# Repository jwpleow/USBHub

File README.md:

## Impedance Control
Impedance control was done assuming manufacturing using JLCPCB 6 layer PCB JLC06161H-7628
90Ohms Diff Pair (usb) -> 0.127mm spacing, 0.16mm trace width
100Ohms Diff Pair (ethernet) -> 0.127mm spacing, 0.11mm trace width

## Min vias
We require 0.15mm/0.25mm vias ($$$$$$$$$$$$)

### Red LED for PD fault
KT-0603R
https://jlcpcb.com/partdetail/Hubei_KentoElec-KT0603R/C2286

## Power
### 5V
| Part Name | Description | Datasheet | JLCPCB |
| - | - | - | - |
| TPS56637RPAR | 4.5-V to 24-V In, 0.6-V to 7-V Out, 8-A Synchronous Step-Down Voltage Regulator | [Datasheet](https://www.ti.com/lit/ds/symlink/tps51396a.pdf) | [JLCPCB](https://jlcpcb.com/partdetail/TexasInstruments-TPS56637RPAR/C841386) | 
| FXL0630-3R3-M | Inductor 3.3uH (max 22mOhm) 8.5A | | [JLCPCB](https://jlcpcb.com/partdetail/178602-FXL0630_3R3M/C167219) |

### 3V3
| Part Name | Description | Datasheet | JLCPCB |
| - | - | - | - |
| TLV75733PDBVR |  Fixed 3.3V 1A SOT-23-5 25uA qI | | [JLCPCB](https://jlcpcb.com/partdetail/TexasInstruments-TLV75733PDBVR/C485517) |

### 1V2
| Part Name | Description | Datasheet | JLCPCB |
| - | - | - | - |
| TPS54331DR | Step-down type Adjustable 0.8V~25V 3A 3.5V~28V Buck converter | [Datasheet](https://www.ti.com/lit/ds/symlink/tps54331.pdf) | [JLCPCB](https://jlcpcb.com/partdetail/TexasInstruments-TPS54331DR/C9865) |
| FNR6045S180MT | Inductor 18uH ±20% 2.4A SMD,6x6mm, 81mOhm |  | [JLCPCB](https://jlcpcb.com/partdetail/179462-FNR6045S180MT/C168079) |

## USB
### Power Delivery

| Part Name | Description | Datasheet | JLCPCB |
| - | - | - | - |
| CYPD3177_24LQXQ | USB Type-C and Power Delivery (PD) Controller QFN-24 | [Datasheet](https://www.infineon.com/dgdl/Infineon-EZ-PD_BCR_Datasheet_USB_Type-C_Port_Controller_for_Power_Sinks-DataSheet-v03_00-EN.pdf?fileId=8ac78c8c7d0d8da4017d0ee7ce9d70ad) | [JLCPCB](https://jlcpcb.com/partdetail/CypressSemicon-CYPD317724LQXQ/C2959321) | 
| BZT52C12 | Zener Diode | | [JLCPCB](https://jlcpcb.com/partdetail/Goodwork-BZT52C12/C2932744) | 
| SI3421DV-T1-GE3 | PMOSFET | | [JLCPCB](https://jlcpcb.com/partdetail/VishayIntertech-SI3421DV_T1GE3/C144884) | 
| SS54 | Schottky Diode for Reverse Polarity Protection | | [JLCPCB](https://jlcpcb.com/partdetail/Hongjiacheng-SS54/C7420369) |

### USB Data

| Part Name | Description | Datasheet | JLCPCB |
| - | - | - | - |
| CYUSB3304-68LTXCT | USB 3.2 Gen1 4-port Hub Controller | [Datasheet](https://www.infineon.com/dgdl/Infineon-CYUSB330x_CYUSB331x_CYUSB332x_HX3_USB_3.0_Hub-DataSheet-v21_00-EN.pdf?fileId=8ac78c8c7d0d8da4017d0ecb53f644b8) | [JLCPCB](https://jlcpcb.com/partdetail/CypressSemicon-CYUSB330468LTXCT/C914921) |
| TUSB522PPRGER | 5Gbps USB3.0 redriver | [Datasheet](https://www.ti.com/lit/ds/symlink/tusb522p.pdf) | [JLCPCB](https://jlcpcb.com/parts/componentSearch?searchTxt=TUSB522P)  |
| PI3USB302-AZBEX | USB 3.0 Passive mux | [Datasheet](https://www.diodes.com/assets/Datasheets/PI3USB302-A.pdf) |  [JLCPCB](https://jlcpcb.com/partdetail/DiodesIncorporated-PI3USB302AZBEX/C500787) |
| TXM26M0004322CBCDO00T | Crystal for USB Hub Controller 26MHz +- 10ppm 9pF | | [JLCPCB](https://jlcpcb.com/partdetail/Yajingxin-TXM26M0004322CBCDO00T/C362346) |
<!-- | TUSB212IRWBR | USB 2.0 Signal Conditioner | [Datasheet](https://www.ti.com/lit/ds/symlink/tusb212.pdf) | [JLCPCB](https://jlcpcb.com/partdetail/TexasInstruments-TUSB212IRWBR/C2674396) | -->

### USB Ancillaries
| Part Name | Description | Datasheet | JLCPCB |
| - | - | - | - |
| GT-USB-7052 | USB Type-C Receptacle USB3.1 5A 24 Pins Vertical SMD | [Datasheet](https://www.dg-switch.com/uploads/soft/200510/GT-USB-7052.pdf) | [JLCPCB](https://jlcpcb.com/partdetail/gswitch-GT_USB7052/C963223) |
| PUSB3FR4Z | ESD Protection for differential pairs | [Datasheet](https://assets.nexperia.com/documents/data-sheet/PUSB3FR4.pdf) | [JLCPCB](https://jlcpcb.com/partdetail/Nexperia-PUSB3FR4Z/C503418)  |
| TI TVS2200DRVR | ESD Protection 28V for VBUS | [Datasheet](https://www.ti.com/lit/ds/symlink/tvs2200.pdf) | [JLCPCB](https://jlcpcb.com/partdetail/TexasInstruments-TVS2200DRVR/C523793) |
| TPS2069CDBVR | 1.5A Current limiting power distribution switch for USB DFP | [Datasheet](https://www.ti.com/lit/ds/symlink/tps2001c.pdf) | [JLCPCB](https://jlcpcb.com/partdetail/TexasInstruments-TPS2069CDBVR/C181752) |
| ESD5B5.0ST1G | 5.8V ESD Protection for DFP VBUS | [Datasheet](https://www.onsemi.com/pdf/datasheet/esd5b5.0st1-d.pdf) | [JLCPCB](https://jlcpcb.com/partdetail/Onsemi-ESD5B50ST1G/C93623) | 
| 484080003 | USB Type A Vertical | | [JLCPCB](https://jlcpcb.com/partdetail/Molex-484080003/C587839) |

### Ethernet USB 
| Part Name | Description | Datasheet | JLCPCB |
| - | - | - | - |
| RTL8153B-VB-CG | Ethernet-USB controller |  | [JLCPCB](https://jlcpcb.com/partdetail/RealtekSemicon-RTL8153B_VBCG/C2802072)  |
| G24P02S | RJ45 Transformer | | [JLCPCB](https://jlcpcb.com/partdetail/Jasn-G24P02S/C2827276)  |
| 7D025000Q01 | 25MHz Crystal, 18pF +- 10ppm | | [JLCPCB](https://jlcpcb.com/partdetail/Hd-7D025000Q01/C648942)|
| RC01931 | Ethernet Port Vertical | | [JLCPCB](https://jlcpcb.com/partdetail/Rch-RC01931/C708651) |

### Others
| Part Name | Description | Datasheet | JLCPCB |
| - | - | - | - |
| KT-0805G | LED Green | | [JLCPCB](https://jlcpcb.com/partdetail/Hubei_KentoElec-KT0805G/C2297) |
| BLM21PG221SN1D | Ferrite Bead 2A @ 85C | | [JLCPCB](https://jlcpcb.com/partdetail/MurataElectronics-BLM21PG221SN1D/C85840) |
| WJ103-5.0-2P | 2P 5mm screw terminal angled | | [JLCPCB](https://jlcpcb.com/partdetail/Ningbo_KangnexElec-WJ103_5_02P/C8439 )  |
| RVT1V151M0607 | 150u Aluminium Electrolytic Capacitor | | [JLCPCB](https://jlcpcb.com/partdetail/Roqang-RVT1V151M0607/C3032176) |
 <!-- | TI TPDxE05U06 | ESD Protection TVS 28V for CC / DP / DM?  | [Datasheet](https://www.ti.com/lit/ds/symlink/tpd4e05u06.pdf) | [JLCPCB](https://jlcpcb.com/partdetail/TexasInstruments-TPD4E05U06DQAR/C138714)  -->

## Buck Converter to 5V

## USB Hub Design Checklist
1 Are the decoupling capacitors and bulk capacitors connected as per Figure 1 and Figure 2? Y
2 Does the crystal meet the specification in this application note?  Y
3 Are all DS ports provided with 150-µF bulk capacitors? Y
4 Do the Power-on-Reset RC components meet the minimum reset time (5 ms)? Y
5 Do the USB precision resistors have 1% tolerance?  Y
6 Are the I2C lines provided with pull-up resistors to the 3.3-V domain? Y
7 Do the LEDs connected to the pin-strap pins have a 10-kΩ parallel resistor? Y
8
Is it ensured that the DS port power switch has a MOSFET connected to the OUTPUT pin or selected a power switch with
fast discharge? Y
9 Is the VBUS_US pin provided with a 10-kΩ voltage divider network? Y
10 Is the US port provided with 1-µF bulk capacitor? N
11 Are all port shields terminated properly?
12 Are the ferrite beads connected as shown in Figure 1 and Figure 2?
13
Are MODE_SEL[1] and MODE_SEL[0] not pulled LOW when the pin-strap configuration is used with HX3? (For 88-pin
QFN only).
14
Are values of the resistors connected in series to the LEDs decided based on the HX3’s I/O current source/sink capability
(4 mA)?
Layout Checklist
1 Is the crystal placed close to the chip (less than 1 cm)?
2 Are the decoupling capacitors and bulk capacitors placed close to the HX3 power pins?
3 Are the vias placed close to the HX3 power pins?
4 Are the power traces routed away from the high-speed data lines and the clock lines?
5 Is the capacitor in the RC reset circuitry placed close to the reset pin of HX3?
6 Is the 150-µF capacitor placed close to the DS port connector?
7 Are the USB SS and HS signal lines matched in length?
8 Are the USB data lines provided with solid ground plane underneath?
9 Are the SS traces provided with the guard traces along the USB data trace with stitching vias?
10 Are the SS traces provided with the AC decoupling capacitors (0.1 µF) on the TX lines?
11 Are the USB traces kept as short as possible?
12 Is it ensured that there are no stubs on all the USB traces?
13 Is it ensured that there are no vias on the SS traces?
14 Do the USB traces have few bends and no 90-degree bends?

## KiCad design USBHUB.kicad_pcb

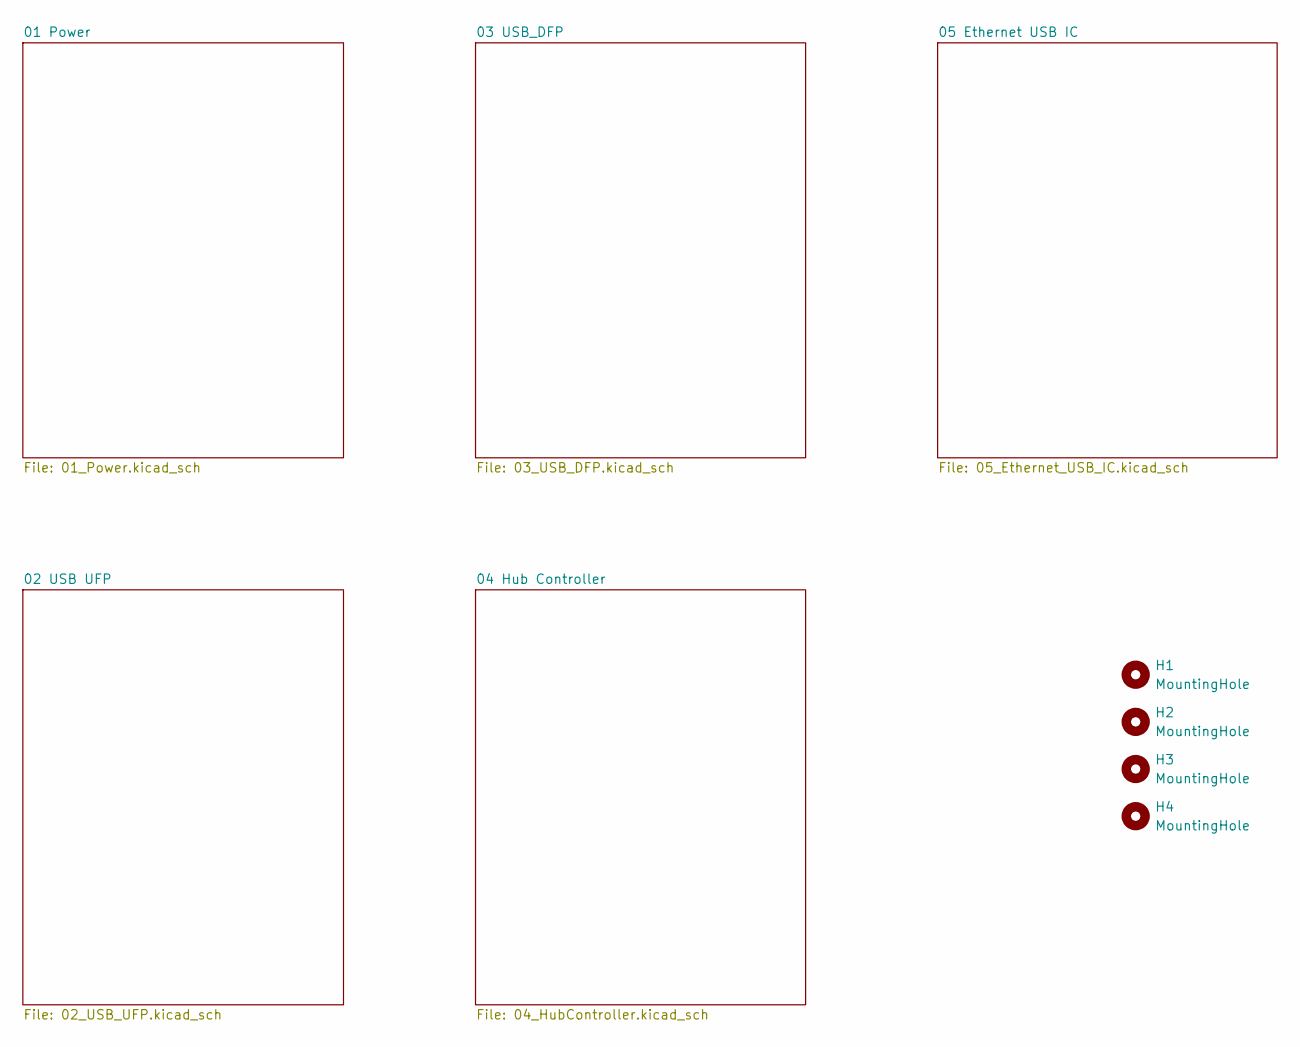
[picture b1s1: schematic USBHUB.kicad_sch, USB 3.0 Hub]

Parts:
H1, H2, H3, H4: MountingHole; MountingHole_2.7mm_M2.5

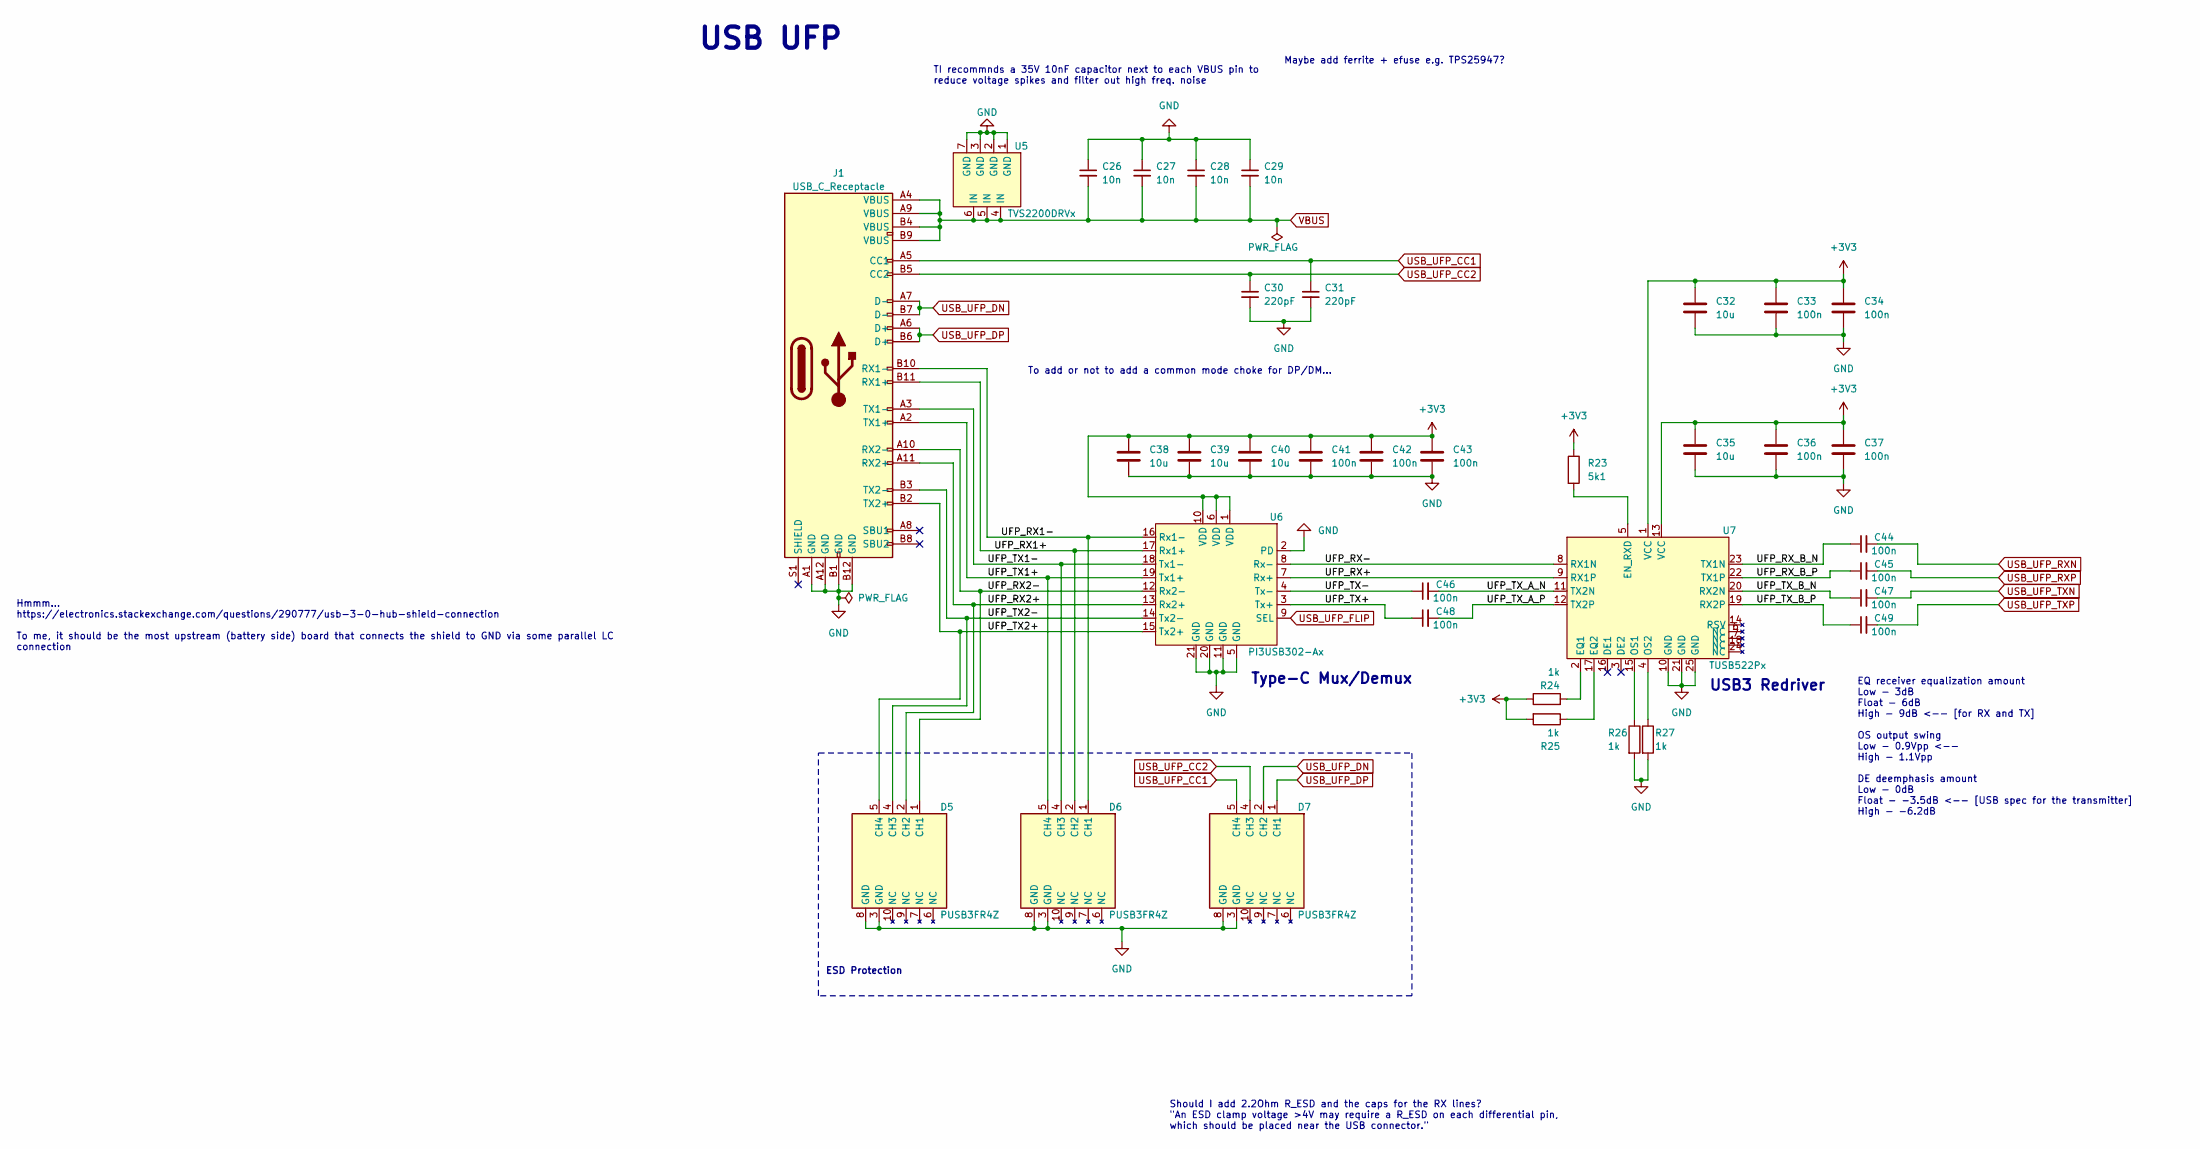
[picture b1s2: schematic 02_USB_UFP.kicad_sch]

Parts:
C26, C27, C28, C29: 10n; C_0402_1005Metric
C30, C31: 220pF; C_0402_1005Metric
C32, C35, C38, C39, C40: 10u; C_0603_1608Metric
C33, C34, C36, C37, C41, C42, C43, C44, C45, C46, C47, C48, C49: 100n; C_0402_1005Metric
D5, D6, D7: PUSB3FR4Z
J1: USB_C_Receptacle; USB_C_Receptacle_GT-USB-7028x
R23: 5k1; R_0603_1608Metric
R24, R25, R26, R27: 1k; R_0603_1608Metric
U5: TVS2200DRVx
U6: PI3USB302-Ax
U7: TUSB522Px

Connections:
+3V3: C32.1, C33.1, C34.1, C35.1, C36.1, C37.1, C38.1, C39.1, C40.1, C41.1, C42.1, C43.1, R23.1, R24.1, R25.2, U6.1 (VDD), U6.6 (VDD), U6.10 (VDD), U7.1 (VCC), U7.13 (VCC); also elsewhere on the board
/02 USB UFP/UFP_RX1+: D6.2 (CH2), J1.B11 (RX1+), U6.17 (Rx1+)
/02 USB UFP/UFP_RX1-: D6.1 (CH1), J1.B10 (RX1-), U6.16 (Rx1-)
/02 USB UFP/UFP_RX2+: D5.2 (CH2), J1.A11 (RX2+), U6.13 (Rx2+)
/02 USB UFP/UFP_RX2-: D5.1 (CH1), J1.A10 (RX2-), U6.12 (Rx2-)
/02 USB UFP/UFP_RX+: U6.7 (Rx+), U7.9 (RX1P)
/02 USB UFP/UFP_RX-: U6.8 (Rx-), U7.8 (RX1N)
/02 USB UFP/UFP_RX_B_N: C44.1, U7.23 (TX1N)
/02 USB UFP/UFP_RX_B_P: C45.1, U7.22 (TX1P)
/02 USB UFP/UFP_TX1+: D6.5 (CH4), J1.A2 (TX1+), U6.19 (Tx1+)
/02 USB UFP/UFP_TX1-: D6.4 (CH3), J1.A3 (TX1-), U6.18 (Tx1-)
/02 USB UFP/UFP_TX2+: D5.5 (CH4), J1.B2 (TX2+), U6.15 (Tx2+)
/02 USB UFP/UFP_TX2-: D5.4 (CH3), J1.B3 (TX2-), U6.14 (Tx2-)
/02 USB UFP/UFP_TX+: C48.1, U6.3 (Tx+)
/02 USB UFP/UFP_TX-: C46.1, U6.4 (Tx-)
/02 USB UFP/UFP_TX_A_N: C46.2, U7.11 (TX2N)
/02 USB UFP/UFP_TX_A_P: C48.2, U7.12 (TX2P)
/02 USB UFP/UFP_TX_B_N: C47.1, U7.20 (RX2N)
/02 USB UFP/UFP_TX_B_P: C49.1, U7.19 (RX2P)
GND: C26.1, C27.1, C28.1, C29.1, C30.2, C31.2, C32.2, C33.2, C34.2, C35.2, C36.2, C37.2, C38.2, C39.2, C40.2, C41.2, C42.2, C43.2, D5.3 (GND), D5.8 (GND), D6.3 (GND), D6.8 (GND), D7.3 (GND), D7.8 (GND), J1.A1 (GND), J1.A12 (GND), J1.B1 (GND), J1.B12 (GND), R26.2, R27.2, U5.1 (GND), U5.2 (GND), U5.3 (GND), U5.7 (GND), U6.2 (PD), U6.5 (GND), U6.11 (GND), U6.20 (GND), U6.21 (GND), U7.10 (GND), U7.21 (GND), U7.25 (GND); also elsewhere on the board
unnamed: R23.2, U7.5 (EN_RXD)
unnamed: R24.2, U7.2 (EQ1)
unnamed: R25.1, U7.17 (EQ2)
unnamed: R26.1, U7.15 (OS1)
unnamed: R27.1, U7.4 (OS2)
USB_UFP_CC1: C31.1, D7.5 (CH4), J1.A5 (CC1); also elsewhere on the board
USB_UFP_CC2: C30.1, D7.4 (CH3), J1.B5 (CC2); also elsewhere on the board
USB_UFP_DN: D7.2 (CH2), J1.A7 (D-), J1.B7 (D-); also elsewhere on the board
USB_UFP_DP: D7.1 (CH1), J1.A6 (D+), J1.B6 (D+); also elsewhere on the board
USB_UFP_FLIP: U6.9 (SEL); also elsewhere on the board
USB_UFP_RXN: C44.2; also elsewhere on the board
USB_UFP_RXP: C45.2; also elsewhere on the board
USB_UFP_TXN: C47.2; also elsewhere on the board
USB_UFP_TXP: C49.2; also elsewhere on the board
VBUS: C26.2, C27.2, C28.2, C29.2, J1.A4 (VBUS), J1.A9 (VBUS), J1.B4 (VBUS), J1.B9 (VBUS), U5.4 (IN), U5.5 (IN), U5.6 (IN); also elsewhere on the board

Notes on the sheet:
TI recommnds a 35V 10nF capacitor next to each VBUS pin to reduce voltage spikes and filter out high freq. noise
Maybe add ferrite + efuse e.g. TPS25947?
Type-C Mux/Demux
ESD Protection
To add or not to add a common mode choke for DP/DM...
EQ receiver equalization amount Low - 3dB Float - 6dB High - 9dB <-- [for RX and TX] OS output swing Low - 0.9Vpp <-- High - 1.1Vpp DE deemphasis amount Low - 0dB Float - -3.5dB <-- [USB spec for the transmitter] High - -6.2dB
USB3 Redriver
Hmmm... https://electronics.stackexchange.com/questions/290777/usb-3-0-hub-shield-connection To me, it should be the most upstream (battery side) board that connects the shield to GND via some parallel LC connection
Should I add 2.2Ohm R_ESD and the caps for the RX lines? "An ESD clamp voltage >4V may require a R_ESD on each differential pin, which should be placed near the USB connector."
USB UFP

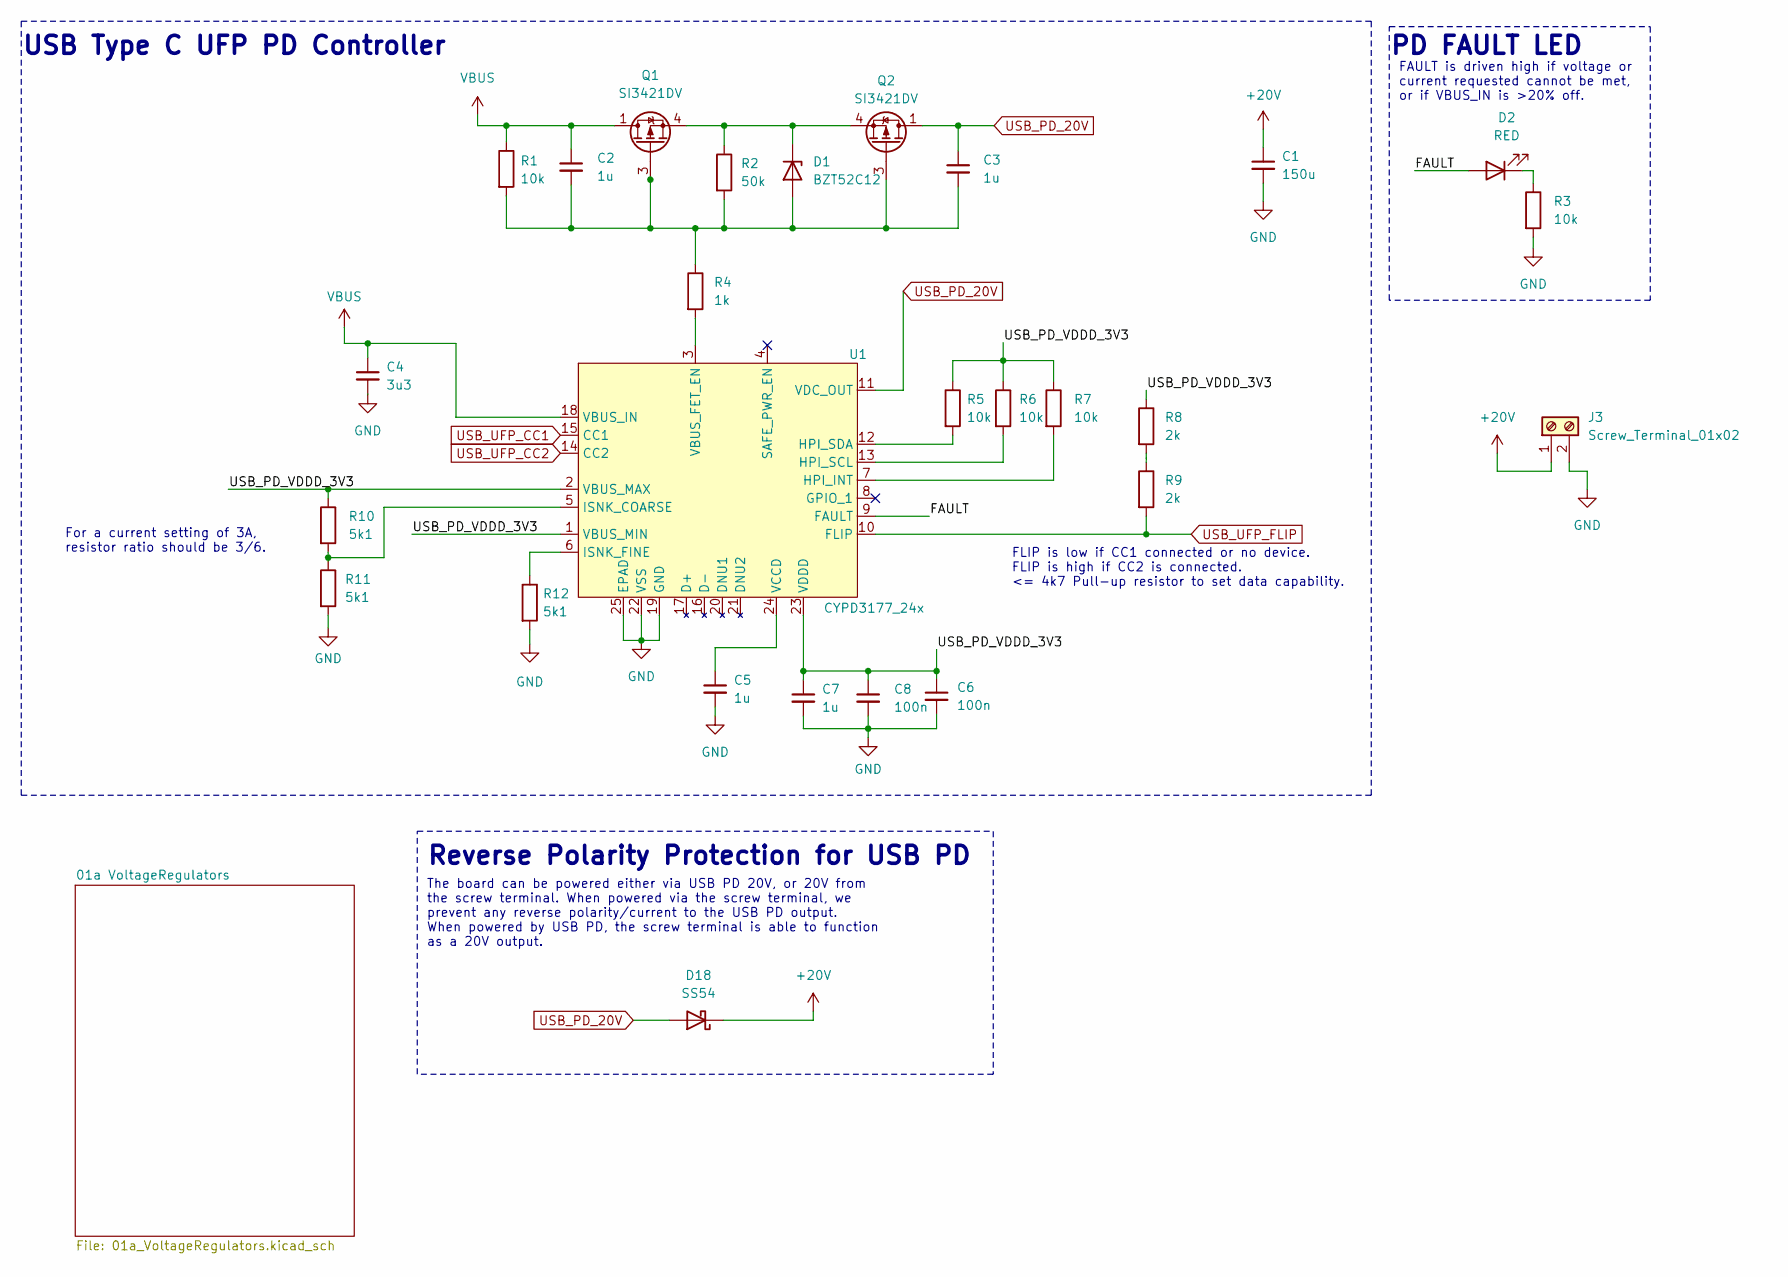
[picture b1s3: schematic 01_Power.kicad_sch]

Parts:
C1: 150u; C_Elec_6.3x7.7
C2, C3, C5, C7: 1u; C_0603_1608Metric
C4: 3u3; C_0603_1608Metric
C6, C8: 100n; C_0603_1608Metric
D1: BZT52C12; D_SOD-123
D2: RED; LED_0603_1608Metric
D18: SS54; D_SMA
J3: Screw_Terminal_01x02; TerminalBlock_WJ103-5.0-2P
Q1, Q2: SI3421DV; SOT-23-6
R1: 10k; R_0603_1608Metric
R2: 50k; R_0603_1608Metric
R3, R5, R6, R7: 10k; R_0402_1005Metric
R4: 1k; R_0603_1608Metric
R8, R9: 2k; R_0402_1005Metric
R10, R11, R12: 5k1; R_0603_1608Metric
U1: CYPD3177_24x; CYPD3177_24LQx_QFN-24_EP_4x4_Pitch0.5mm

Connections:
+20V: C1.1, D18.1 (K), J3.1; also elsewhere on the board
/01 Power/FAULT: D2.2 (A), U1.9 (FAULT)
/01 Power/USB_PD_VDDD_3V3: C6.1, C7.1, C8.1, R5.1, R6.1, R7.1, R8.1, R10.1, U1.1 (VBUS_MIN), U1.2 (VBUS_MAX), U1.23 (VDDD)
GND: C1.2, C4.2, C5.2, C6.2, C7.2, C8.2, J3.2, R3.2, R11.2, R12.2, U1.19 (GND), U1.22 (VSS), U1.25 (EPAD); also elsewhere on the board
unnamed: C2.2, C3.2, D1.2 (A), Q1.3 (G), Q2.3 (G), R1.2, R2.2, R4.1
unnamed: D1.1 (K), Q1.4 (S), Q2.4 (S), R2.1
unnamed: D2.1 (K), R3.1
unnamed: R8.2, R9.1
unnamed: R7.2, U1.7 (HPI_INT)
unnamed: R6.2, U1.13 (HPI_SCL)
unnamed: R5.2, U1.12 (HPI_SDA)
unnamed: R10.2, R11.1, U1.5 (ISNK_COARSE)
unnamed: R12.1, U1.6 (ISNK_FINE)
unnamed: R4.2, U1.3 (VBUS_FET_EN)
unnamed: C5.1, U1.24 (VCCD)
USB_PD_20V: C3.1, D18.2 (A), Q2.1 (D), Q2.2 (D1), Q2.5 (D2), Q2.6 (D3), U1.11 (VDC_OUT)
USB_UFP_CC1: U1.15 (CC1); also elsewhere on the board
USB_UFP_CC2: U1.14 (CC2); also elsewhere on the board
USB_UFP_FLIP: R9.2, U1.10 (FLIP); also elsewhere on the board
VBUS: C2.1, C4.1, Q1.1 (D), Q1.2 (D1), Q1.5 (D2), Q1.6 (D3), R1.1, U1.18 (VBUS_IN); also elsewhere on the board

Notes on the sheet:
For a current setting of 3A, resistor ratio should be 3/6.
FLIP is low if CC1 connected or no device. FLIP is high if CC2 is connected. <= 4k7 Pull-up resistor to set data capability.
USB Type C UFP PD Controller
PD FAULT LED
The board can be powered either via USB PD 20V, or 20V from the screw terminal. When powered via the screw terminal, we prevent any reverse polarity/current to the USB PD output. When powered by USB PD, the screw terminal is able to function as a 20V output.
Reverse Polarity Protection for USB PD
FAULT is driven high if voltage or current requested cannot be met, or if VBUS_IN is >20% off.

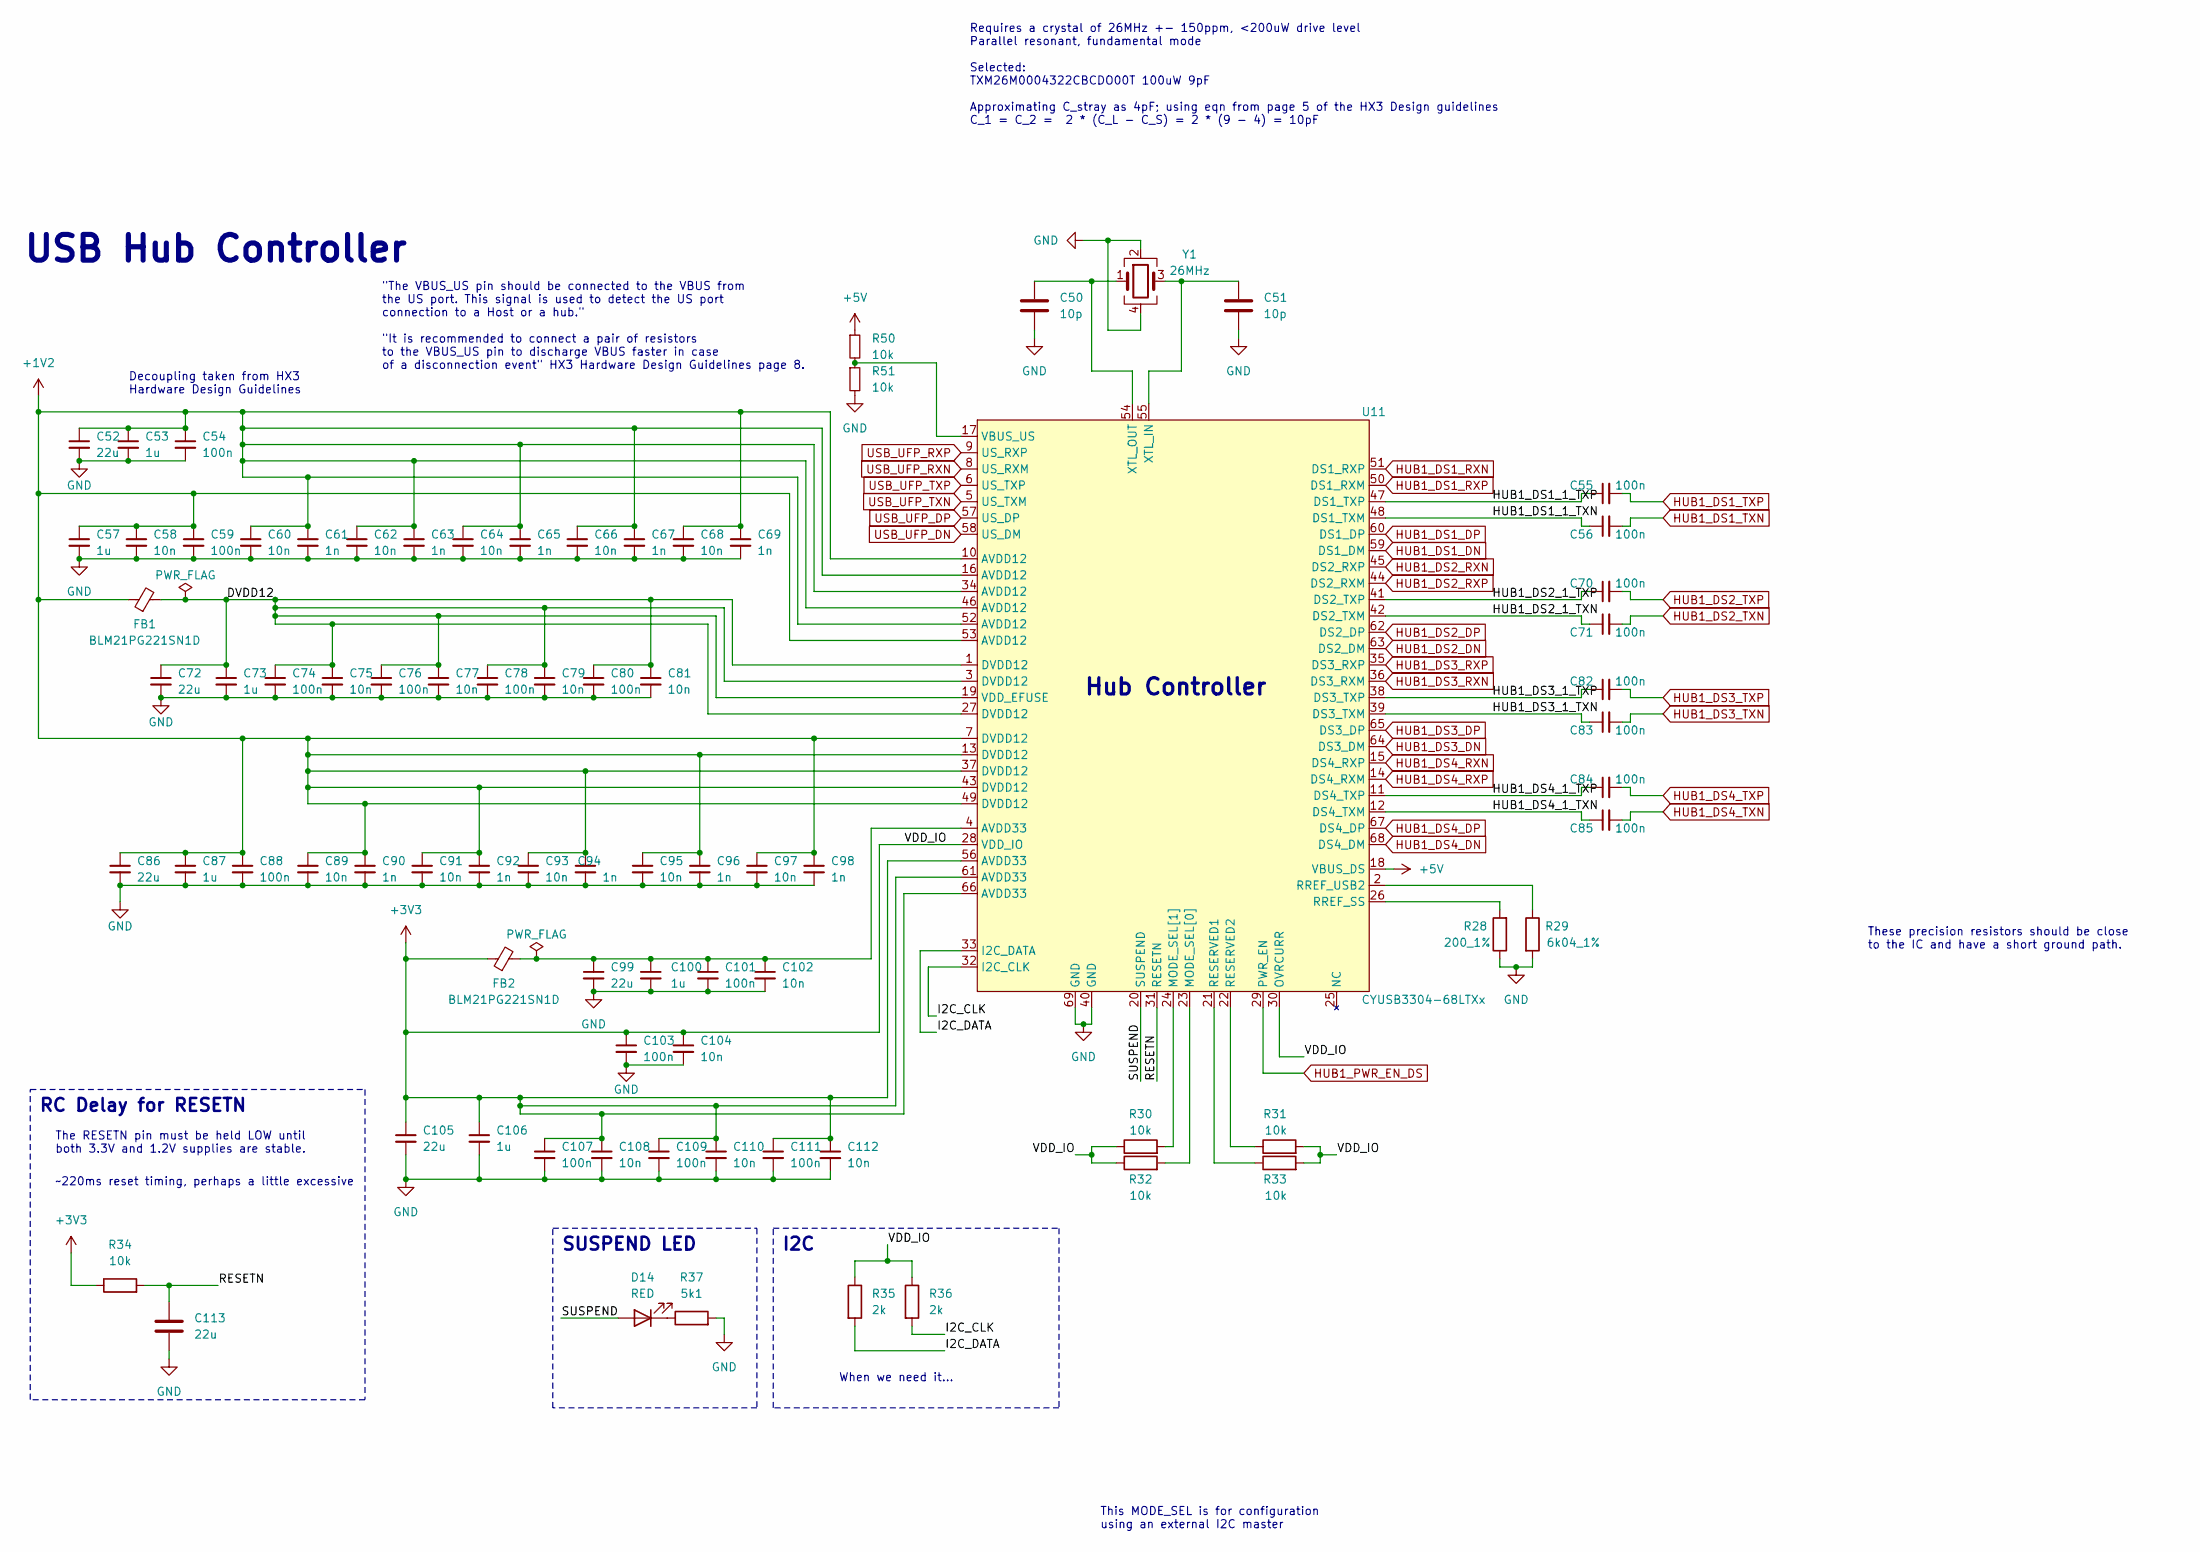
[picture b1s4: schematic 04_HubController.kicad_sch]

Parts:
C50, C51: 10p; C_0402_1005Metric
C52, C72, C86, C99, C105, C113: 22u; C_0603_1608Metric
C53, C57, C73, C87, C100, C106: 1u; C_0603_1608Metric
C54, C55, C56, C59, C70, C71, C74, C76, C78, C80, C82, C83, C84, C85, C88, C101, C103, C107, C109, C111: 100n; C_0402_1005Metric
C58, C60, C62, C64, C66, C68, C75, C77, C79, C81, C89, C91, C93, C95, C97, C102, C104, C108, C110, C112: 10n; C_0402_1005Metric
C61, C63, C65, C67, C69, C90, C92, C94, C96, C98: 1n; C_0402_1005Metric
D14: RED; LED_0603_1608Metric
FB1, FB2: BLM21PG221SN1D; L_0805_2012Metric
R28: 200_1%; R_0402_1005Metric
R29: 6k04_1%; R_0402_1005Metric
R30, R31, R32, R33, R34, R50, R51: 10k; R_0402_1005Metric
R35, R36: 2k; R_0402_1005Metric
R37: 5k1; R_0603_1608Metric
U11: CYUSB3304-68LTXx
Y1: 26MHz; Crystal_SMD_3225-4Pin_3.2x2.5mm

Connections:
+1V2: C52.1, C53.1, C54.1, C57.1, C58.1, C59.1, C60.1, C61.1, C62.1, C63.1, C64.1, C65.1, C66.1, C67.1, C68.1, C69.1, C86.1, C87.1, C88.1, C89.1, C90.1, C91.1, C92.1, C93.1, C94.1, C95.1, C96.1, C97.1, C98.1, FB1.1, U11.7 (DVDD12), U11.10 (AVDD12), U11.13 (DVDD12), U11.16 (AVDD12), U11.34 (AVDD12), U11.37 (DVDD12), U11.43 (DVDD12), U11.46 (AVDD12), U11.49 (DVDD12), U11.52 (AVDD12), U11.53 (AVDD12); also elsewhere on the board
+3V3: C103.1, C104.1, C105.1, C106.1, C107.1, C108.1, C109.1, C110.1, C111.1, C112.1, FB2.1, R30.1, R31.2, R32.1, R33.2, R34.1, R35.1, R36.1, U11.28 (VDD_IO), U11.30 (OVRCURR), U11.56 (AVDD33), U11.61 (AVDD33), U11.66 (AVDD33); also elsewhere on the board
+5V: R50.1, U11.18 (VBUS_DS); also elsewhere on the board
/04 Hub Controller/DVDD12: C72.1, C73.1, C74.1, C75.1, C76.1, C77.1, C78.1, C79.1, C80.1, C81.1, FB1.2, U11.1 (DVDD12), U11.3 (DVDD12), U11.19 (VDD_EFUSE), U11.27 (DVDD12)
/04 Hub Controller/HUB1_DS1_1_TXN: C56.1, U11.48 (DS1_TXM)
/04 Hub Controller/HUB1_DS1_1_TXP: C55.1, U11.47 (DS1_TXP)
/04 Hub Controller/HUB1_DS2_1_TXN: C71.1, U11.42 (DS2_TXM)
/04 Hub Controller/HUB1_DS2_1_TXP: C70.1, U11.41 (DS2_TXP)
/04 Hub Controller/HUB1_DS3_1_TXN: C83.1, U11.39 (DS3_TXM)
/04 Hub Controller/HUB1_DS3_1_TXP: C82.1, U11.38 (DS3_TXP)
/04 Hub Controller/HUB1_DS4_1_TXN: C85.1, U11.12 (DS4_TXM)
/04 Hub Controller/HUB1_DS4_1_TXP: C84.1, U11.11 (DS4_TXP)
/04 Hub Controller/I2C_CLK: R36.2, U11.32 (I2C_CLK)
/04 Hub Controller/I2C_DATA: R35.2, U11.33 (I2C_DATA)
/04 Hub Controller/RESETN: C113.1, R34.2, U11.31 (RESETN)
/04 Hub Controller/SUSPEND: D14.2 (A), U11.20 (SUSPEND)
GND: C50.2, C51.2, C52.2, C53.2, C54.2, C57.2, C58.2, C59.2, C60.2, C61.2, C62.2, C63.2, C64.2, C65.2, C66.2, C67.2, C68.2, C69.2, C72.2, C73.2, C74.2, C75.2, C76.2, C77.2, C78.2, C79.2, C80.2, C81.2, C86.2, C87.2, C88.2, C89.2, C90.2, C91.2, C92.2, C93.2, C94.2, C95.2, C96.2, C97.2, C98.2, C99.2, C100.2, C101.2, C102.2, C103.2, C104.2, C105.2, C106.2, C107.2, C108.2, C109.2, C110.2, C111.2, C112.2, C113.2, R28.1, R29.2, R37.2, R51.2, U11.40 (GND), U11.69 (GND), Y1.2, Y1.4; also elsewhere on the board
HUB1_DS1_DN: U11.59 (DS1_DM); also elsewhere on the board
HUB1_DS1_DP: U11.60 (DS1_DP); also elsewhere on the board
HUB1_DS1_RXN: U11.51 (DS1_RXP); also elsewhere on the board
HUB1_DS1_RXP: U11.50 (DS1_RXM); also elsewhere on the board
HUB1_DS1_TXN: C56.2; also elsewhere on the board
HUB1_DS1_TXP: C55.2; also elsewhere on the board
HUB1_DS2_DN: U11.63 (DS2_DM); also elsewhere on the board
HUB1_DS2_DP: U11.62 (DS2_DP); also elsewhere on the board
HUB1_DS2_RXN: U11.45 (DS2_RXP); also elsewhere on the board
HUB1_DS2_RXP: U11.44 (DS2_RXM); also elsewhere on the board
HUB1_DS2_TXN: C71.2; also elsewhere on the board
HUB1_DS2_TXP: C70.2; also elsewhere on the board
HUB1_DS3_DN: U11.64 (DS3_DM); also elsewhere on the board
HUB1_DS3_DP: U11.65 (DS3_DP); also elsewhere on the board
HUB1_DS3_RXN: U11.36 (DS3_RXM); also elsewhere on the board
HUB1_DS3_RXP: U11.35 (DS3_RXP); also elsewhere on the board
HUB1_DS3_TXN: C83.2; also elsewhere on the board
HUB1_DS3_TXP: C82.2; also elsewhere on the board
HUB1_DS4_DN: U11.68 (DS4_DM); also elsewhere on the board
HUB1_DS4_DP: U11.67 (DS4_DP); also elsewhere on the board
HUB1_DS4_RXN: U11.15 (DS4_RXP); also elsewhere on the board
HUB1_DS4_RXP: U11.14 (DS4_RXM); also elsewhere on the board
HUB1_DS4_TXN: C85.2; also elsewhere on the board
HUB1_DS4_TXP: C84.2; also elsewhere on the board
HUB1_PWR_EN_DS: U11.29 (PWR_EN); also elsewhere on the board
unnamed: C99.1, C100.1, C101.1, C102.1, FB2.2, U11.4 (AVDD33)
unnamed: D14.1 (K), R37.1
unnamed: R32.2, U11.23 (MODE_SEL[0])
unnamed: R30.2, U11.24 (MODE_SEL[1])
unnamed: R33.1, U11.21 (RESERVED1)
unnamed: R31.1, U11.22 (RESERVED2)
unnamed: R28.2, U11.26 (RREF_SS)
unnamed: R29.1, U11.2 (RREF_USB2)
unnamed: R50.2, R51.1, U11.17 (VBUS_US)
unnamed: C51.1, U11.55 (XTL_IN), Y1.3
unnamed: C50.1, U11.54 (XTL_OUT), Y1.1
USB_UFP_DN: U11.58 (US_DM); also elsewhere on the board
USB_UFP_DP: U11.57 (US_DP); also elsewhere on the board
USB_UFP_RXN: U11.8 (US_RXM); also elsewhere on the board
USB_UFP_RXP: U11.9 (US_RXP); also elsewhere on the board
USB_UFP_TXN: U11.5 (US_TXM); also elsewhere on the board
USB_UFP_TXP: U11.6 (US_TXP); also elsewhere on the board

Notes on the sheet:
RC Delay for RESETN
These precision resistors should be close to the IC and have a short ground path.
Decoupling taken from HX3 Hardware Design Guidelines
SUSPEND LED
USB Hub Controller
Hub Controller
When we need it...
This MODE_SEL is for configuration using an external I2C master
~220ms reset timing, perhaps a little excessive
I2C
The RESETN pin must be held LOW until both 3.3V and 1.2V supplies are stable.
"The VBUS_US pin should be connected to the VBUS from the US port. This signal is used to detect the US port connection to a Host or a hub." "It is recommended to connect a pair of resistors to the VBUS_US pin to discharge VBUS faster in case of a disconnection event" HX3 Hardware Design Guidelines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
Requires a crystal of 26MHz +- 150ppm, <200uW drive level Parallel resonant, fundamental mode Selected: TXM26M0004322CBCDO00T 100uW 9pF Approximating C_stray as 4pF; using eqn from page 5 of the HX3 Design guidelines C_1 = C_2 = 2 * (C_L - C_S) = 2 * (9 - 4) = 10pF

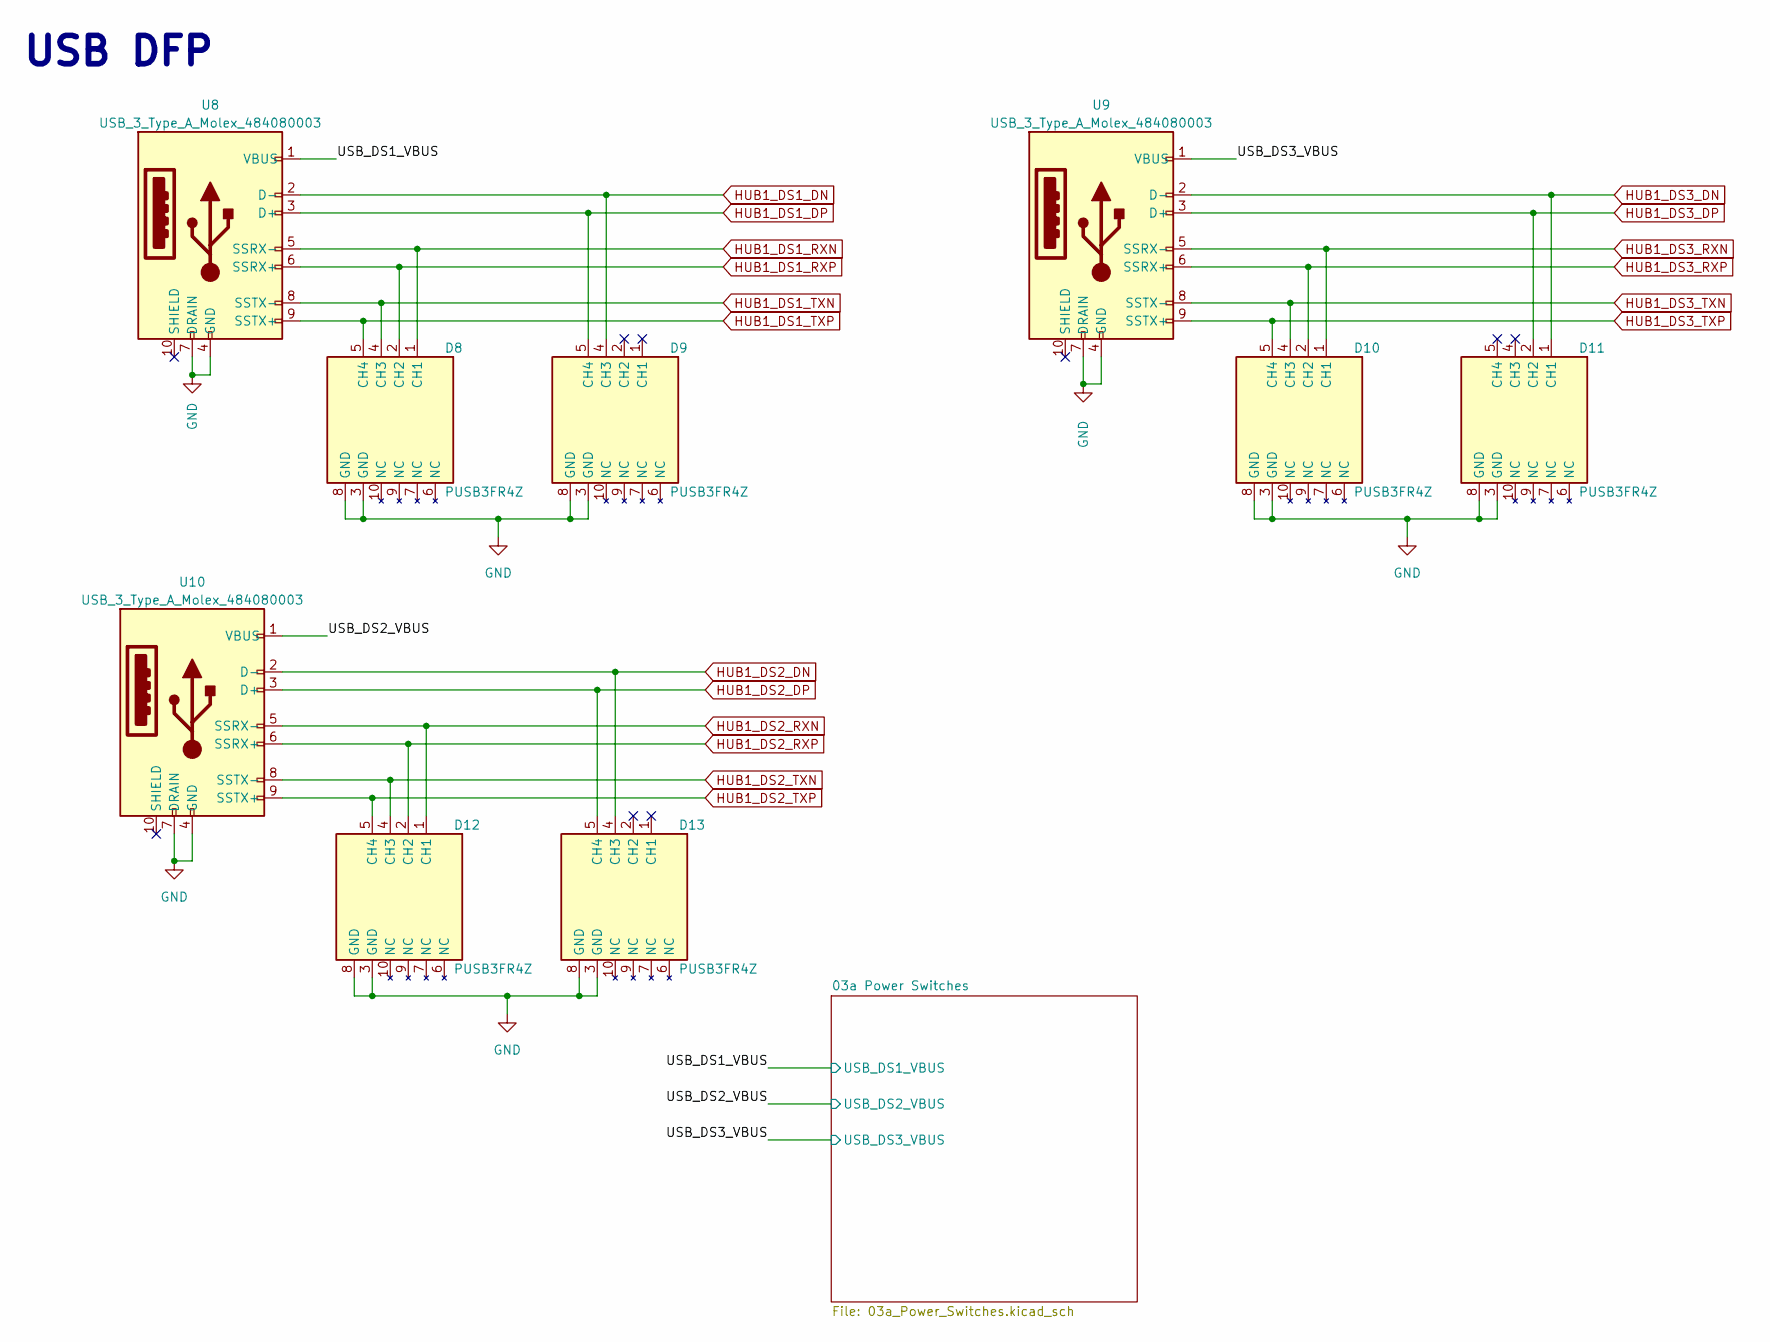
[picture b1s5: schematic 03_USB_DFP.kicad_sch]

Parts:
D8, D9, D10, D11, D12, D13: PUSB3FR4Z
U8, U9, U10: USB_3_Type_A_Molex_484080003; Molex_484080003

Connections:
/03 USB_DFP/USB_DS1_VBUS: U8.1 (VBUS); also elsewhere on the board
/03 USB_DFP/USB_DS2_VBUS: U10.1 (VBUS); also elsewhere on the board
/03 USB_DFP/USB_DS3_VBUS: U9.1 (VBUS); also elsewhere on the board
GND: D8.3 (GND), D8.8 (GND), D9.3 (GND), D9.8 (GND), D10.3 (GND), D10.8 (GND), D11.3 (GND), D11.8 (GND), D12.3 (GND), D12.8 (GND), D13.3 (GND), D13.8 (GND), U8.4 (GND), U8.7 (DRAIN), U9.4 (GND), U9.7 (DRAIN), U10.4 (GND), U10.7 (DRAIN); also elsewhere on the board
HUB1_DS1_DN: D9.4 (CH3), U8.2 (D-); also elsewhere on the board
HUB1_DS1_DP: D9.5 (CH4), U8.3 (D+); also elsewhere on the board
HUB1_DS1_RXN: D8.1 (CH1), U8.5 (SSRX-); also elsewhere on the board
HUB1_DS1_RXP: D8.2 (CH2), U8.6 (SSRX+); also elsewhere on the board
HUB1_DS1_TXN: D8.4 (CH3), U8.8 (SSTX-); also elsewhere on the board
HUB1_DS1_TXP: D8.5 (CH4), U8.9 (SSTX+); also elsewhere on the board
HUB1_DS2_DN: D13.4 (CH3), U10.2 (D-); also elsewhere on the board
HUB1_DS2_DP: D13.5 (CH4), U10.3 (D+); also elsewhere on the board
HUB1_DS2_RXN: D12.1 (CH1), U10.5 (SSRX-); also elsewhere on the board
HUB1_DS2_RXP: D12.2 (CH2), U10.6 (SSRX+); also elsewhere on the board
HUB1_DS2_TXN: D12.4 (CH3), U10.8 (SSTX-); also elsewhere on the board
HUB1_DS2_TXP: D12.5 (CH4), U10.9 (SSTX+); also elsewhere on the board
HUB1_DS3_DN: D11.1 (CH1), U9.2 (D-); also elsewhere on the board
HUB1_DS3_DP: D11.2 (CH2), U9.3 (D+); also elsewhere on the board
HUB1_DS3_RXN: D10.1 (CH1), U9.5 (SSRX-); also elsewhere on the board
HUB1_DS3_RXP: D10.2 (CH2), U9.6 (SSRX+); also elsewhere on the board
HUB1_DS3_TXN: D10.4 (CH3), U9.8 (SSTX-); also elsewhere on the board
HUB1_DS3_TXP: D10.5 (CH4), U9.9 (SSTX+); also elsewhere on the board

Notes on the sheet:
USB DFP
